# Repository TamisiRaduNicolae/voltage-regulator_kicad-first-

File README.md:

# voltage-regulator_kicad-first-
first kicad project ; simple voltage regulator 5v - 3.3v
this project was my first in kicad and it was a simple and ilustrative way to help me get familiar with the basics and the workflow of kicad 9. 
fun experience

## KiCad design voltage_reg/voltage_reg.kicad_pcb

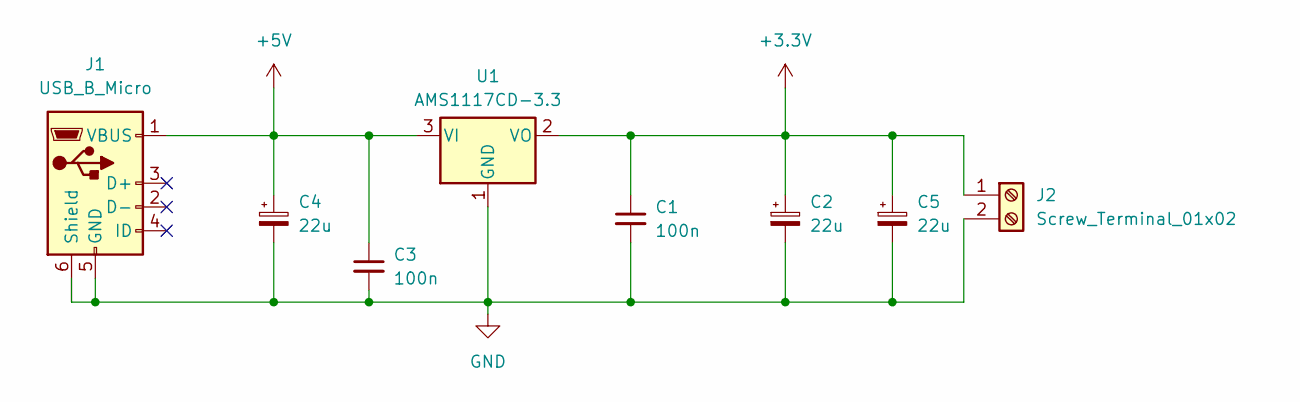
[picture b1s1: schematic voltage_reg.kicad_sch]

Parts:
C1, C3: 100n; C_0402_1005Metric
C2, C4, C5: 22u; CP_Elec_6.3x7.7
J1: USB_B_Micro; USB_Micro-B_Molex_47346-0001
J2: Screw_Terminal_01x02; TerminalBlock_MaiXu_MX126-5.0-02P_1x02_P5.00mm
U1: AMS1117CD-3.3; TO-252-3_TabPin2

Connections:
+3.3V: C1.1, C2.1, C5.1, J2.1, U1.2 (VO)
+5V: C3.1, C4.1, J1.1 (VBUS), U1.3 (VI)
GND: C1.2, C2.2, C3.2, C4.2, C5.2, J1.5 (GND), J1.6 (Shield), J2.2, U1.1 (GND)

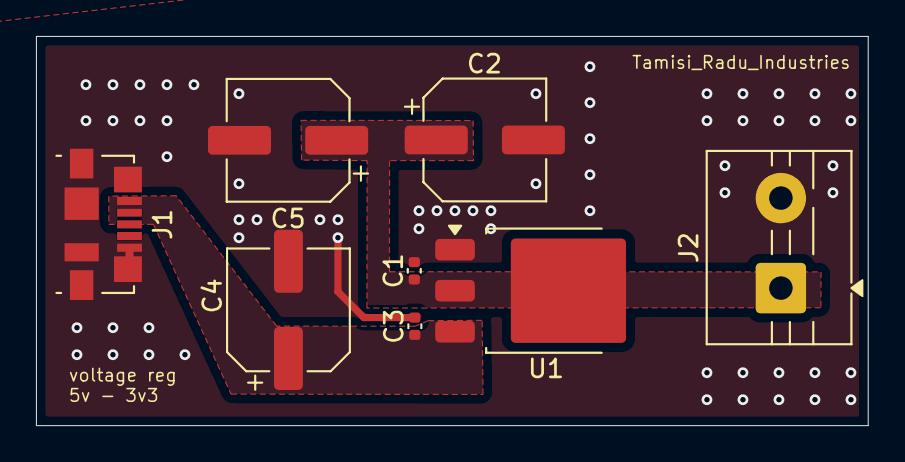
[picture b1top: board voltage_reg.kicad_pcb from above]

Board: 2 copper layers, 46.2 x 21.6 mm, 8 parts (0 on the bottom side), 3 nets.

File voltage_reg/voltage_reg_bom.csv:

"Id";"Designator";"Footprint";"Quantity";"Designation";"Supplier and ref";
1;"C5,C2,C4";"CP_Elec_6.3x7.7";3;"22u";;;
2;"J2";"TerminalBlock_MaiXu_MX126-5.0-02P_1x02_P5.00mm";1;"Screw_Terminal_01x02";;;
3;"C3,C1";"C_0402_1005Metric";2;"100n";;;
4;"J1";"USB_Micro-B_Molex_47346-0001";1;"USB_B_Micro";;;
5;"U1";"TO-252-3_TabPin2";1;"AMS1117CD-3.3";;;

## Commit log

2025-09-25 added gitignore for kicad
2025-09-25 added the schematic
2025-09-25 started to work on the pcb and poured some traces for 5v and 3v3
2025-09-26 finished traces and saved fabrication output files, such as gerbers and drill files, and also a 3D view in png form
2025-09-26 updated the readme
